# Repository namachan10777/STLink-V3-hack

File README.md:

# STLink-V3-hack
Provide power source by STLink

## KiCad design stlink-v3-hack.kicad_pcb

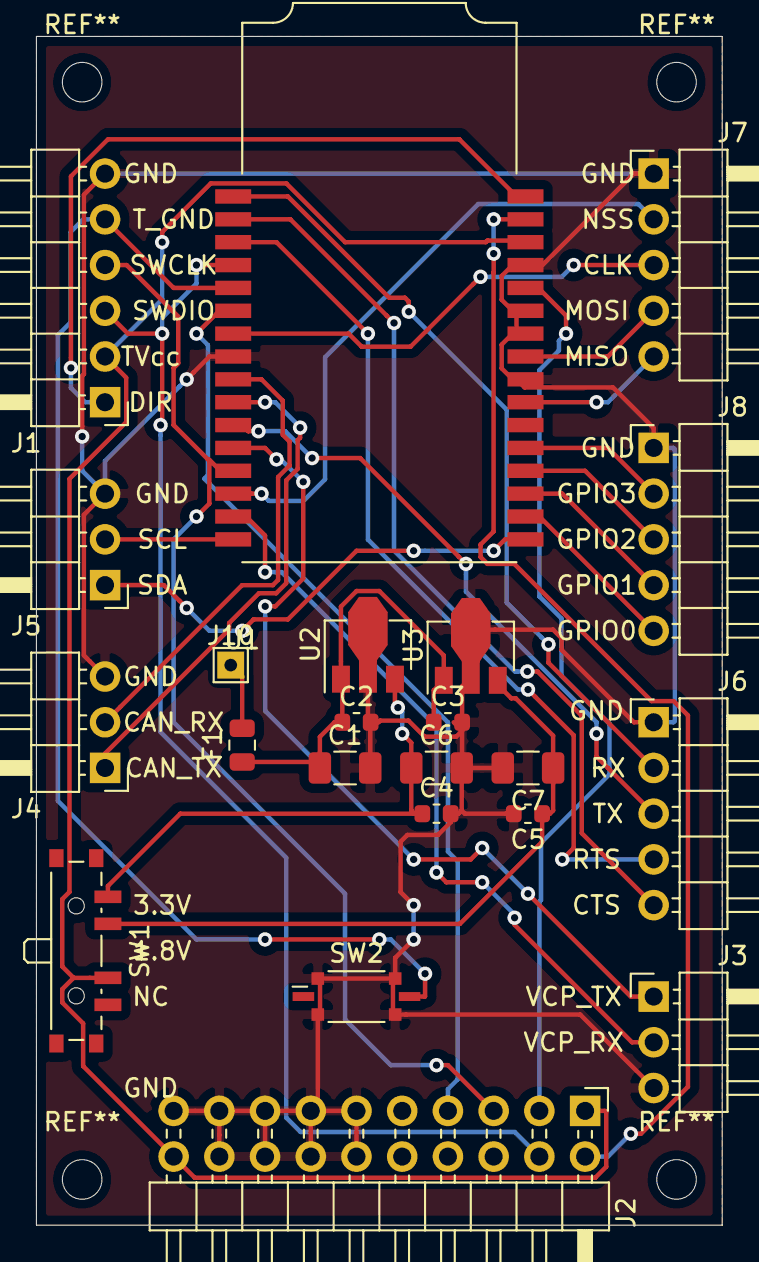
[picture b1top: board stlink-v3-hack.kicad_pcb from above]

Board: 2 copper layers, 38.1 x 66.0 mm, 22 parts (0 on the bottom side), 31 nets.

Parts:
C1, C6, C7: 1uF; C_1206_3216Metric
C2, C3, C4, C5: 0.1uF; C_0603_1608Metric
F1: Polyfuse; Fuse_0805_2012Metric
J1: SW; PinHeader_1x06_P2.54mm_Horizontal
J2: JTAG; PinHeader_2x10_P2.54mm_Horizontal
J3: VCP; PinHeader_1x03_P2.54mm_Horizontal
J4: Bridge_CAN; PinHeader_1x03_P2.54mm_Horizontal
J5: Bridge_I2C; PinHeader_1x03_P2.54mm_Horizontal
J6: Bridge_UART; PinHeader_1x05_P2.54mm_Horizontal
J7: SPI; PinHeader_1x05_P2.54mm_Horizontal
J8: GPIO; PinHeader_1x05_P2.54mm_Horizontal
J10: VUSB_Jumpered; TestPoint_THTPad_1.5x1.5mm_Drill0.7mm
SW1: POWER_SELECT; SW_SP3T_PCM13
SW2: SW_SPDT; SW_DIP_SPSTx01_Slide_Copal_CVS-01xB_W5.9mm_P1mm
U1: STLINK-V3MINI
U2: Regul3.3V; SOT-89-3
U3: Regul1.8V; SOT-89-3

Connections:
+1V8: C5.1, C7.1, SW1.2, U3.3
+3V3: C4.1, C6.1, SW1.1, U2.3
/CAN_RX: J4.2, U1.9
/CAN_TX: J4.1, U1.10
/GPIO0: J8.5, U1.18
/GPIO1: J8.4, U1.19
/GPIO2: J8.3, U1.20
/GPIO3: J8.2, U1.21
/SCL: J5.2, U1.16
/SDA: J5.1, U1.17
/SPI_CLK: J7.3, U1.7
/SPI_MISO: J7.5, U1.23
/SPI_MOSI: J7.4, U1.25
/SPI_NSS: J7.2, U1.14
/SWCLK: J1.4, J2.5, U1.13
/SWDIO: J1.3, J2.4, U1.4
/T_GND: J1.5, SW2.2, U1.5
/T_JTDI: J2.3, U1.28
/T_JTDO: J2.7, U1.6
/T_NRST: J2.2, U1.31
/T_SW_DIR: J1.1, U1.32
/T_VCP_RX: J3.2, U1.15
/T_VCP_TX: J3.1, U1.12
/T_Vcc: J1.2, J2.1, J2.20, SW1.3, U1.30
/UART_CTS: J6.5, U1.2
/UART_RTS: J6.4, U1.3
/UART_RX: J6.2, U1.1
/UART_TX: J6.3, U1.11
GND: C1.2, C2.2, C3.2, C4.2, C5.2, C6.2, C7.2, J1.6, J2.11, J2.12, J2.13, J2.14, J2.15, J2.16, J2.17, J2.18, J2.19, J3.3, J4.3, J5.3, J6.1, J7.1, J8.1, SW2.3, U1.8, U1.24, U1.26, U1.27, U1.29, U2.2, U3.2
unnamed: C1.1, C2.1, C3.1, F1.1, U2.1, U3.1
unnamed: F1.2, J10.1

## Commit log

2020-03-04 add schematic
2020-03-04 fix pinheader's angle
2020-03-06 add footprint for STLINK-V3MINI
2020-03-06 fix gitignore
2020-03-08 fix label
2020-03-08 prod
